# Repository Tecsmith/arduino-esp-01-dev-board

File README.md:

# Development board for ESP-01

| Board | URL |
|---|---|
| [ESP-01 Qwiic Development Board](https://tecsmith.github.io/arduino-esp-01-dev-board/) | [`c1k.it/esp1`](http://c1k.it/esp1) |

## Help, About, *etc.*

Refer to the [docs folder](docs/index.md).

<p align="center" style="color:#069">★</p>

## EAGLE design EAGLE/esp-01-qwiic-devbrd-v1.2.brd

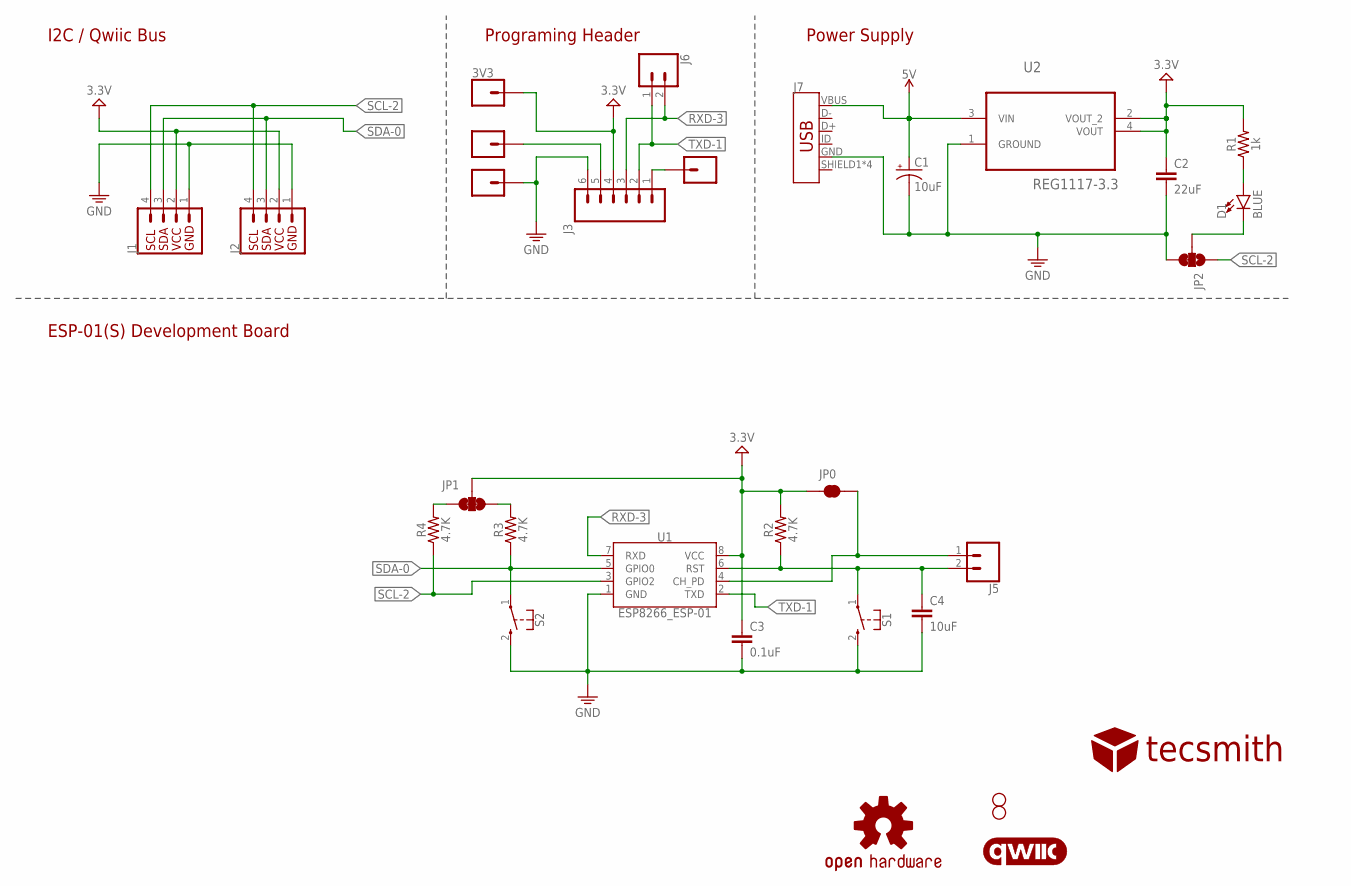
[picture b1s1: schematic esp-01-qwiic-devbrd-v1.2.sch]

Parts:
3V3: CONN_01PTH_NO_SILK_YES_STOP; 1X01_NO_SILK
C1: 10uF; EIA3216
C2: 22uF; 0805
C3: 0.1uF; 0603
C4: 10uF; 0805
D1: BLUE; LED-0603
H1, H2: STAND-OFF
J1: QWIIC_RIGHT_ANGLE; JST04_1MM_RA
J2: I2C_STANDARD; 1X04
J3: CONN_06NO_SILK_FEMALE_PTH; 1X06_NO_SILK
J4, J8, J9: CONN_01PTH_NO_SILK_YES_STOP; 1X01_NO_SILK
J5: CONN_02; 1X02
J6: CONN_021X02_NO_SILK; 1X02_NO_SILK
J7: USB_MICRO-B_FEMALE-SMT; USB-B-MICRO-SMD
JP0: JUMPER-SMT_2_NC_TRACE_SILK; SMT-JUMPER_2_NC_TRACE_SILK
JP1: JUMPER-SMT_3_2-NC_TRACE_SILK; SMT-JUMPER_3_2-NC_TRACE_SILK
JP2: JUMPER-SMT_3_1-NC_TRACE_SILK; SMT-JUMPER_3_1-NC_TRACE_SILK
LOGO1: OSHW-LOGOS; OSHW-LOGO-S
LOGO2: QWIIC_LOGO_6MM; QWIIC_6MM
R1: 1k; 0603
R2, R3, R4: 4.7K; 0805
S1, S2: MOMENTARY-SWITCH-SPST-1; SKRKAEE020
U1: ESP8266_ESP-01
U2: REG1117-3.3; SOT230P700X180-4N
U$1: TECSMITH-LOGO

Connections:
5V: C1.+, J7.VBUS, U2.3 (VIN)
CTS: J3.5, J8.1
DTR: J3.1, J9.1
EN: J5.1, JP0.2, U1.4 (CH_PD)
GND: C1.-, C2.2, C3.2, C4.2, J1.1, J2.1, J3.6, J4.1, J7.GND, JP2.3, S1.2 (3), S2.2 (3), U1.1 (GND), U2.1 (GROUND)
unnamed: D1.C, JP2.2
unnamed: D1.A, R1.1
unnamed: JP1.3, R4.2
unnamed: JP1.1, R3.2
RST: C4.1, J5.2, R2.1, S1.1, U1.6 (RST)
RXD-3: J3.3, J6.2, U1.7 (RXD)
SCL-2: J1.4, J2.4, JP2.1, R4.1, U1.3 (GPIO2)
SDA-0: J1.3, J2.3, R3.1, S2.1, U1.5 (GPIO0)
TXD-1: J3.2, J6.1, U1.2 (TXD)
VCC: 3V3.1, C2.1, C3.1, J1.2, J2.2, J3.4, JP0.1, JP1.2, R1.2, R2.2, U1.8 (VCC), U2.2 (VOUT_2), U2.4 (VOUT)

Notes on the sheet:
I2C / Qwiic Bus
Programing Header
Power Supply
ESP-01(S) Development Board

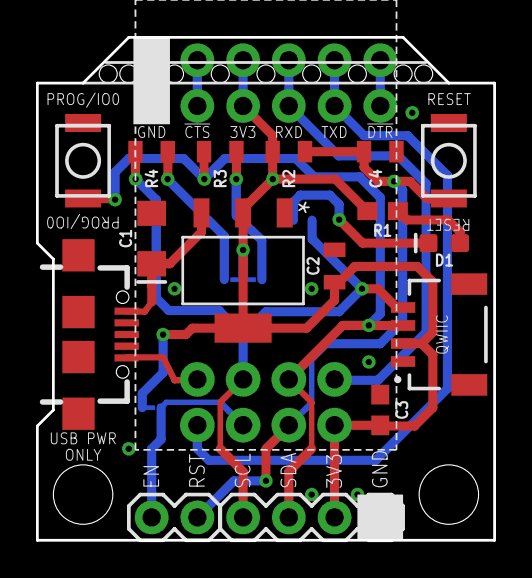
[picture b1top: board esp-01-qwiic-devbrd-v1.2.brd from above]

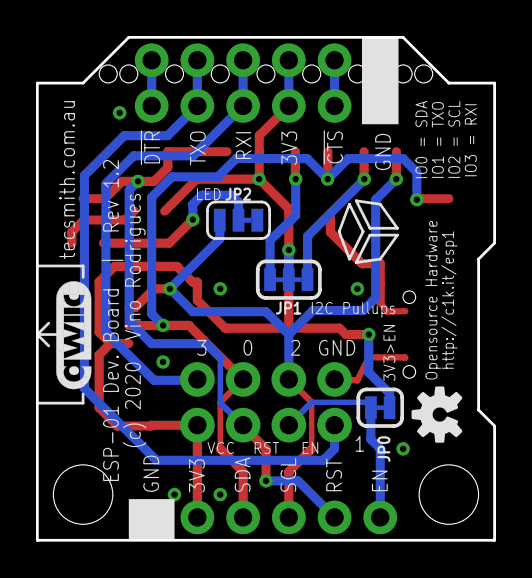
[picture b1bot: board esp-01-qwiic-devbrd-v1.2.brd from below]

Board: 2 copper layers, 25.4 x 27.9 mm, 31 parts (6 on the bottom side), 15 nets.

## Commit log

2021-07-04 moved from fan-control project
2021-07-04 Set theme jekyll-theme-cayman
2021-07-04 uploaded docs
2021-07-09 moving more files from the fan-control project
2021-07-11 vendor docs

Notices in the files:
EAGLE/esp-01-qwiic-devbrd-v1.2.brd:
(c) 2020  Vino Rodrigues
parts and their libraries:
SparkFun-Aesthetics: Licensing: Creative Commons ShareAlike 4.0 International - https://creativecommons.org/licenses/by-sa/4.0
